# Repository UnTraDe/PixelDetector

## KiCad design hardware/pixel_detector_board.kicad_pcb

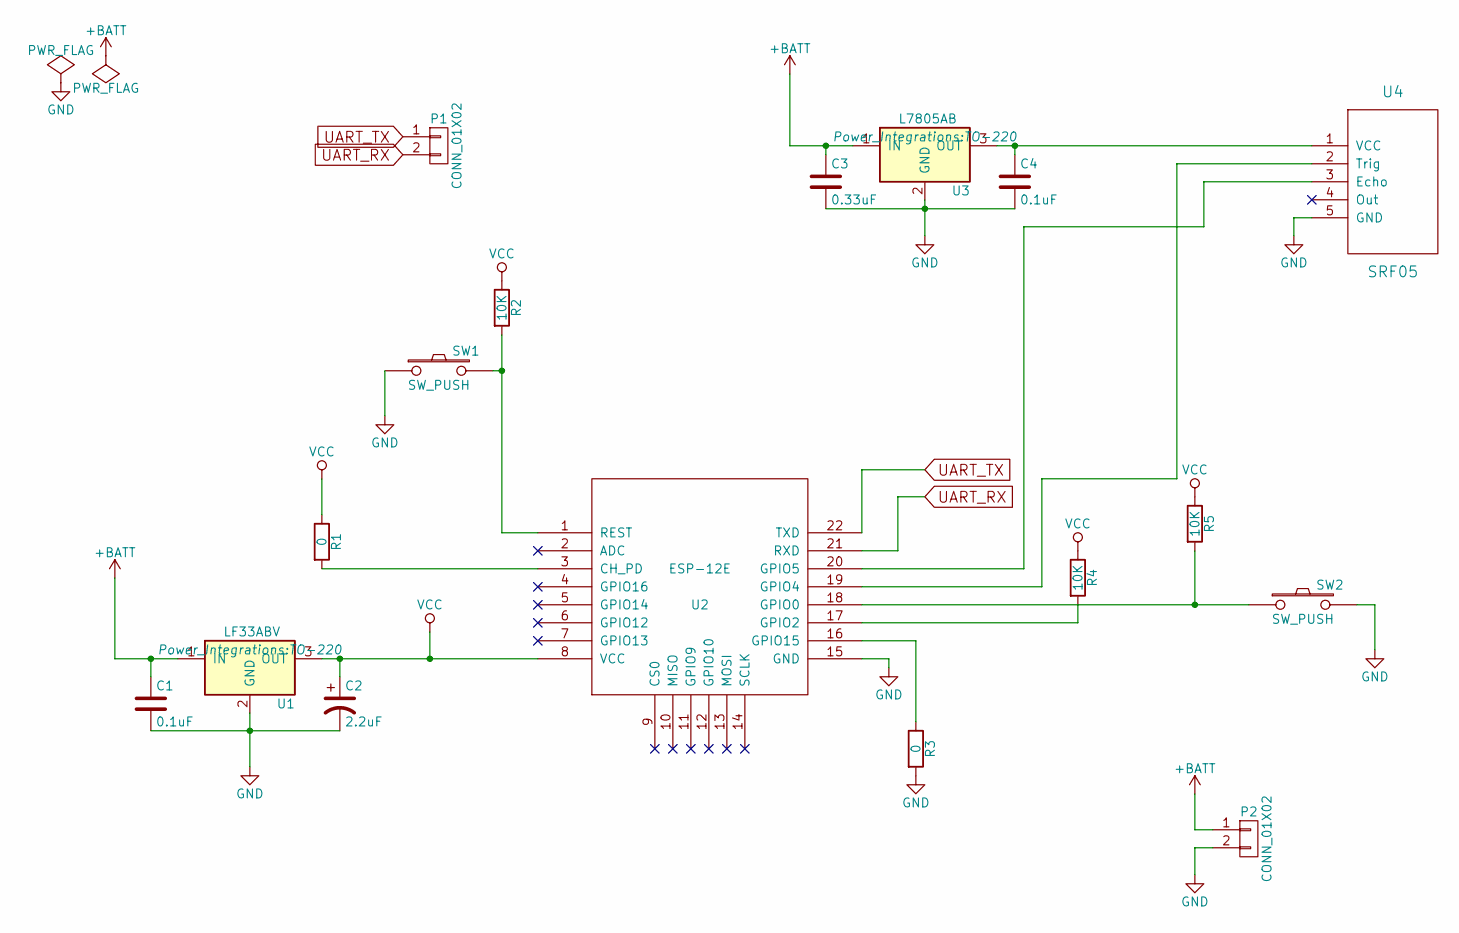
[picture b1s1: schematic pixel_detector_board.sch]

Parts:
C1, C4: 0.1uF; C_Radial_D5_L6_P2.5
C2: 2.2uF; C_Radial_D5_L6_P2.5
C3: 0.33uF; C_Radial_D5_L6_P2.5
P1, P2: CONN_01X02; Pin_Header_Straight_1x02
R1, R3: 0; Resistor_Horizontal_RM7mm
R2, R4, R5: 10K; Resistor_Horizontal_RM7mm
SW1, SW2: SW_PUSH; SW_PUSH_6mm
U1: LF33ABV; TO-220
U2: ESP-12E
U3: L7805AB; TO-220
U4: SRF05; Pin_Header_Straight_1x05

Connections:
+BATT: C1.1, C3.1, P2.1, U1.1 (IN), U3.1 (IN)
GND: C1.2, C2.2, C3.2, C4.2, P2.2, R3.2, SW1.1, SW2.2, U1.2 (GND), U2.15 (GND), U3.2 (GND), U4.5 (GND)
unnamed: C4.1, U3.3 (OUT), U4.1 (VCC)
unnamed: R1.2, U2.3 (CH_PD)
unnamed: R2.2, SW1.2, U2.1 (REST)
unnamed: R3.1, U2.16 (GPIO15)
unnamed: R4.2, U2.17 (GPIO2)
unnamed: R5.2, SW2.1, U2.18 (GPIO0)
unnamed: U2.19 (GPIO4), U4.2 (Trig)
unnamed: U2.20 (GPIO5), U4.3 (Echo)
UART_RX: P1.2, U2.21 (RXD)
UART_TX: P1.1, U2.22 (TXD)
VCC: C2.1, R1.1, R2.1, R4.1, R5.1, U1.3 (OUT), U2.8 (VCC)

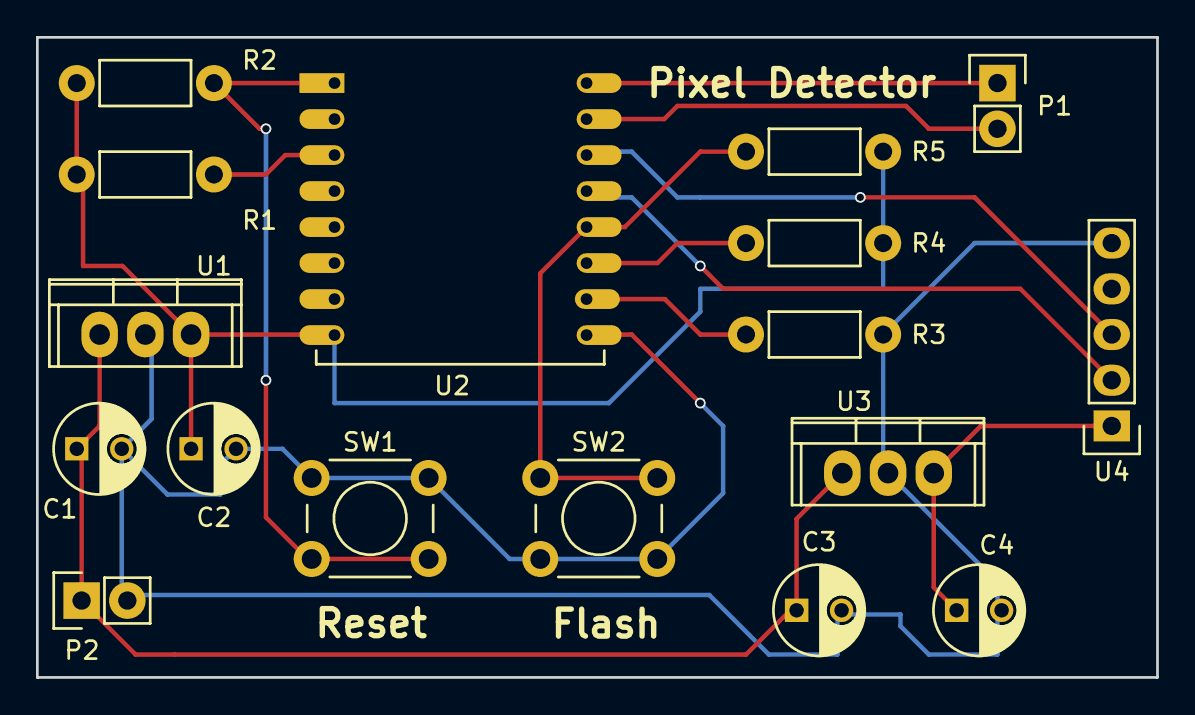
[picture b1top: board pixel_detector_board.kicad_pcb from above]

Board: 2 copper layers, 62.2 x 35.6 mm, 17 parts (0 on the bottom side), 13 nets.

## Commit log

2016-12-16 name changed
2016-12-16 typo
2016-12-17 algorithm + sleep
2016-12-17 small refactor
2016-12-17 removed old include
2016-12-17 debug battery measurements
